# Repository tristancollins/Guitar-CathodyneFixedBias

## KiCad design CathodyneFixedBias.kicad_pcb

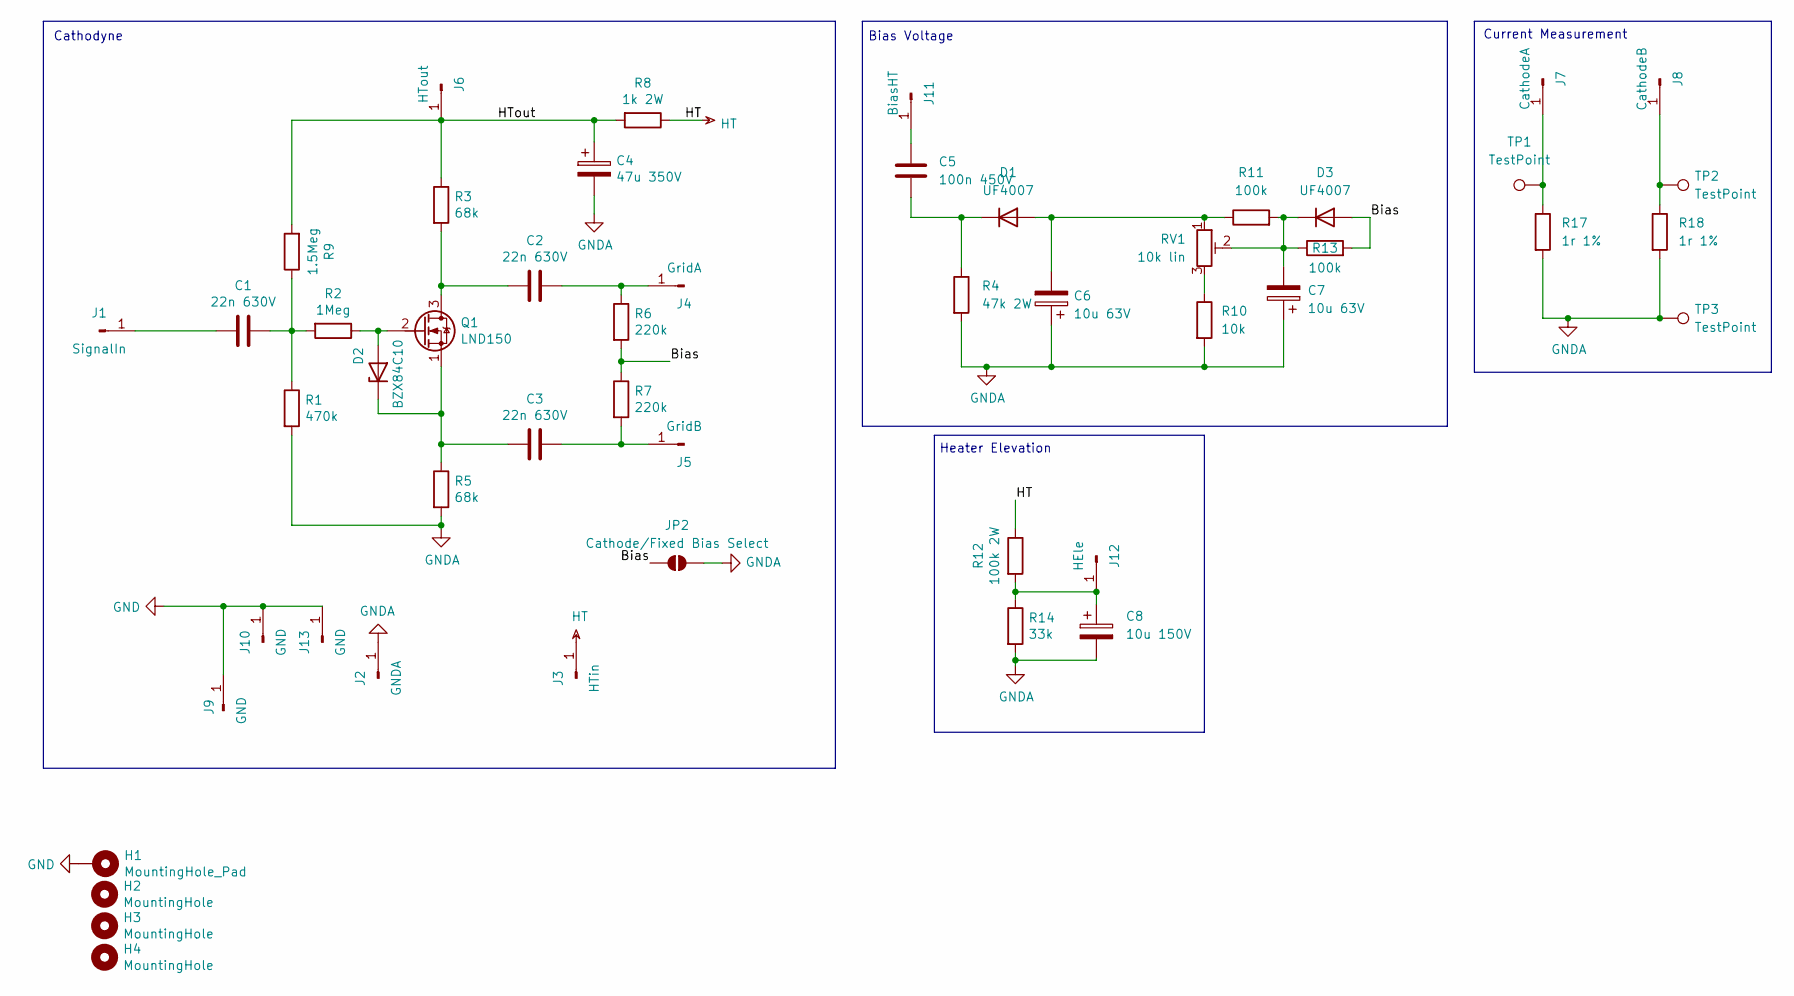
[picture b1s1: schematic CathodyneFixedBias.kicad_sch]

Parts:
C1, C2, C3: 22n 630V; C_Rect_L13.0mm_W4.0mm_P10.00mm_FKS3_FKP3_MKS4; MPN 1928-MKS4J022203C00KSSD-ND
C4: 47u 350V; CP_Radial_D12.5mm_P5.00mm; MPN 493-4839-1-ND
C5: 100n 450V; C_Rect_L18.0mm_W8.0mm_P15.00mm_FKS3_FKP3; MPN 399-12597-ND
C6, C7: 10u 63V; CP_Radial_D5.0mm_P2.50mm; MPN 399-18269-1-ND
C8: 10u 150V; CP_Radial_D8.0mm_P3.50mm; MPN 493-12828-1-ND
D1, D3: UF4007; D_DO-35_SOD27_P2.54mm_Vertical_AnodeUp; MPN 4878-UF4007CT-ND
D2: BZX84C10; D_A-405_P7.62mm_Horizontal; MPN 1514-1N4104TRPBFREECT-ND
H1: MountingHole_Pad; MountingHole_3.2mm_M3_Pad_Via
H2, H3, H4: MountingHole; MountingHole_3.2mm_M3
J1: SignalIn; SolderWire-0.5sqmm_1x01_D0.9mm_OD2.1mm
J2: GNDA; SolderWire-0.5sqmm_1x01_D0.9mm_OD2.1mm
J3: HTin; SolderWire-0.5sqmm_1x01_D0.9mm_OD2.1mm
J4: GridA; SolderWire-0.5sqmm_1x01_D0.9mm_OD2.1mm
J5: GridB; SolderWire-0.5sqmm_1x01_D0.9mm_OD2.1mm
J6: HTout; SolderWire-0.5sqmm_1x01_D0.9mm_OD2.1mm
J7: CathodeA; SolderWire-0.5sqmm_1x01_D0.9mm_OD2.1mm
J8: CathodeB; SolderWire-0.5sqmm_1x01_D0.9mm_OD2.1mm
J9, J10, J13: GND; SolderWire-0.5sqmm_1x01_D0.9mm_OD2.1mm
J11: BiasHT; SolderWire-0.5sqmm_1x01_D0.9mm_OD2.1mm
J12: HEle; SolderWire-0.5sqmm_1x01_D0.9mm_OD2.1mm
JP2: Cathode/Fixed Bias Select; SolderJumper-2_P1.3mm_Open_RoundedPad1.0x1.5mm
Q1: LND150; TO-92_HandSolder; MPN LND150N3-G-ND
R1: 470k; R_Axial_DIN0207_L6.3mm_D2.5mm_P7.62mm_Horizontal_TC; MPN 1712-LR1F470KCT-ND
R2: 1Meg; R_Axial_DIN0207_L6.3mm_D2.5mm_P7.62mm_Horizontal_TC; MPN A105954CT-ND
R3, R5: 68k; R_Axial_DIN0207_L6.3mm_D2.5mm_P7.62mm_Horizontal_TC; MPN 1712-LR1F68KCT-ND
R4: 47k 2W; R_Axial_DIN0309_L9.0mm_D3.2mm_P5.08mm_Vertical; MPN A138333CT-ND
R6, R7: 220k; R_Axial_DIN0207_L6.3mm_D2.5mm_P7.62mm_Horizontal_TC; MPN 1712-LR1F220KCT-ND
R8: 1k 2W; R_Axial_DIN0309_L9.0mm_D3.2mm_P12.70mm_Horizontal; MPN A138277CT-ND
R9: 1.5Meg; R_Axial_DIN0207_L6.3mm_D2.5mm_P7.62mm_Horizontal_TC; MPN BC3622CT-ND
R10: 10k; R_Axial_DIN0207_L6.3mm_D2.5mm_P7.62mm_Horizontal_TC; MPN A105947CT-ND
R11, R13: 100k; R_Axial_DIN0207_L6.3mm_D2.5mm_P7.62mm_Horizontal_TC; MPN A105945CT-ND
R12: 100k 2W; R_Axial_DIN0309_L9.0mm_D3.2mm_P12.70mm_Horizontal; MPN A131612CT-ND
R14: 33k; R_Axial_DIN0207_L6.3mm_D2.5mm_P7.62mm_Horizontal_TC; MPN 1712-LR1F33KCT-ND
R17, R18: 1r 1%; R_Axial_DIN0207_L6.3mm_D2.5mm_P7.62mm_Horizontal_TC; MPN 1712-LR1F1R0CT-ND
RV1: 10k lin; Potentiometer_Bourns_3296X_Horizontal; MPN 3296X-503LF-ND
TP1, TP2, TP3: TestPoint; TestPoint_Keystone_5005-5009_Compact

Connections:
/Bias: D3.2 (A), JP2.2 (B), R6.2, R7.1, R13.2
/HTout: C4.1, J6.1, R3.1, R8.2, R9.2
GND: H1.1, J9.1, J10.1, J13.1
GNDA: C4.2, C6.1, C7.1, C8.2, J2.1, JP2.1 (A), R1.2, R4.2, R5.2, R10.2, R14.2, R17.2, R18.2, TP3.1
HT: J3.1, R8.1, R12.1
unnamed: C1.1, R1.1, R2.2, R9.1
unnamed: C6.2, D1.2 (A), R11.1, RV1.1
unnamed: C5.2, D1.1 (K), R4.1
unnamed: D2.2 (A), Q1.2 (G), R2.1
unnamed: C3.2, D2.1 (K), Q1.1 (S), R5.1
unnamed: C7.2, D3.1 (K), R11.2, R13.1, RV1.2
unnamed: C1.2, J1.1
unnamed: C2.1, J4.1, R6.1
unnamed: C3.1, J5.1, R7.2
unnamed: J7.1, R17.1, TP1.1
unnamed: J8.1, R18.1, TP2.1
unnamed: C5.1, J11.1
unnamed: C8.1, J12.1, R12.2, R14.1
unnamed: C2.2, Q1.3 (D), R3.2
unnamed: R10.1, RV1.3

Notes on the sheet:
Current Measurement
Bias Voltage
Cathodyne
Heater Elevation

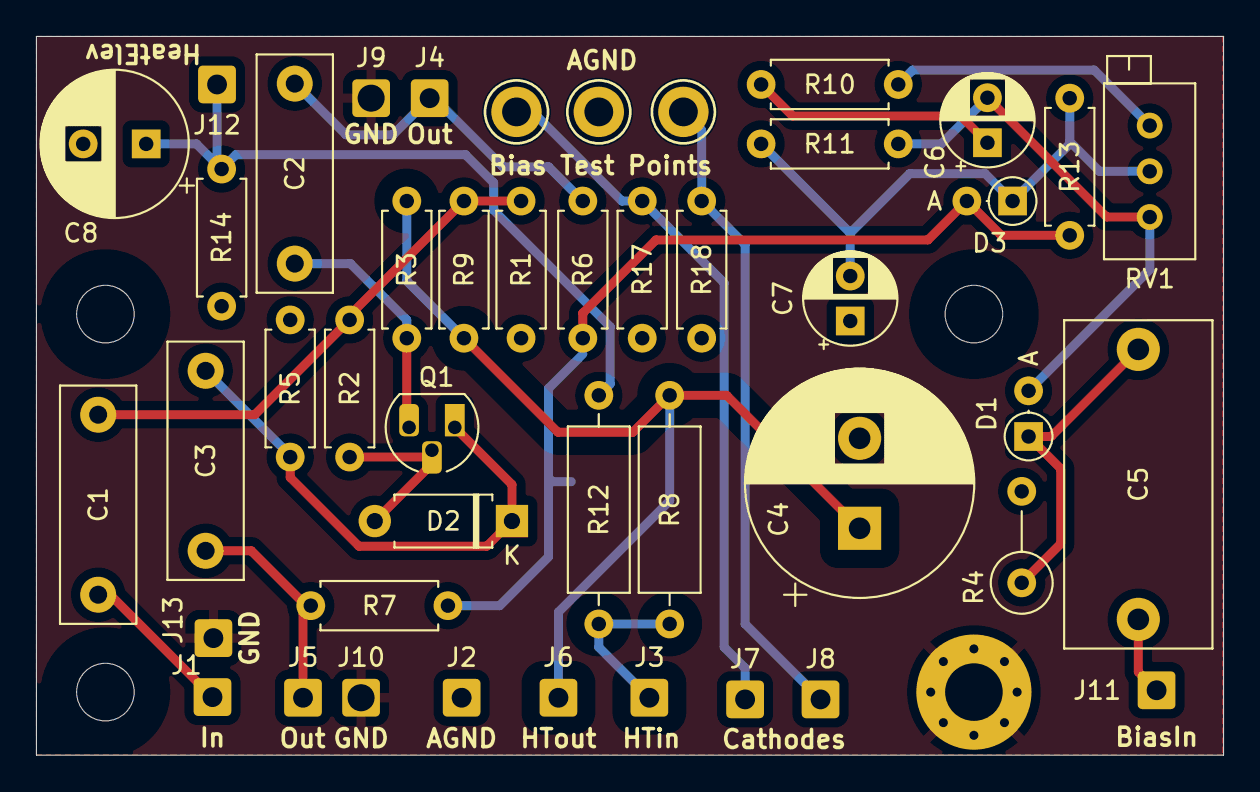
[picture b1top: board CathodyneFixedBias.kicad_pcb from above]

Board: 2 copper layers, 66.0 x 39.9 mm, 50 parts (1 on the bottom side), 20 nets.

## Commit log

2024-12-12 version sent to production
2024-12-12 adding other files needed
2025-03-11 fixed ground error, added new shield point
2025-03-11 added pdf
